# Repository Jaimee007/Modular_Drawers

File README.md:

# Modular_Drawers

Cajonera modular inteligente impresa en 3D. Cada unidad de retícula lleva su propio microcontrolador (CH32V003), un LED RGB y un final de carrera. Los módulos se unen con cola de milano y se conectan entre sí con latiguillos de cable plano IDC. Un ESP32-C3 en el módulo base **descubre automáticamente la posición de cada cajón** y lo integra con Home Assistant, para encender el cajón donde está lo que buscas.

## Documentación

La documentación está separada en cuatro niveles, del "qué" al "cómo". **Si solo vas a leer uno, lee el primero.**

| # | Archivo | Contenido | Cambia cuando… |
|---|---|---|---|
| 1 | [docs/01_especificacion_funcional.md](docs/01_especificacion_funcional.md) | **Qué hace el sistema**: requisitos, comportamiento, estados, criterios de aceptación. Sin un número de pin dentro | …cambia el comportamiento del producto |
| 2 | [docs/02_diseno_hardware.md](docs/02_diseno_hardware.md) | **Cómo está construido**: arquitectura, componentes, protocolo del bus, alimentación, mecánica | …se cambia un componente o una decisión técnica |
| 3 | [docs/03_diseno_pcb.md](docs/03_diseno_pcb.md) | **Las placas en KiCad**: esquemáticos, layout, reglas de diseño, pedido a JLCPCB | …se rediseña una placa |
| 4 | [docs/04_diseno_software.md](docs/04_diseno_software.md) | **El código**: firmware del módulo y del controlador, integración en HA, plan de pruebas por fases | …cambia el firmware |

Y aparte:

| Archivo | Contenido |
|---|---|
| [docs/bom_5_cajones.md](docs/bom_5_cajones.md) | Lista de materiales para un prototipo de 5 cajones, con referencias de LCSC y JLCPCB |

## Herramientas

- `tools/gen_esquematico.py`: genera un esquemático de referencia en HTML. Uso: `python tools/gen_esquematico.py` (solo librería estándar de Python).

## Resumen técnico

| | |
|---|---|
| **Retícula** | 50 mm. Profundidad 130 mm |
| **Un módulo = una unidad de retícula** | Un cajón 1×1 es un módulo; un 2×1 son dos módulos emparejados. **Una sola placa para todo** |
| **Micro por módulo** | CH32V003F4P6 (TSSOP-20), ~0,15 $ |
| **Dirección** | 1–31, por 5 puentes de soldadura |
| **Emparejamiento** | 2 puentes direccionales (pareja a la izquierda / abajo) |
| **Bus entre módulos** | Cable plano de 6 hilos: GND, 5V, DATA, SENSE, GND, 5V. **Box header 2×3 en las cuatro caras**; el cable nunca se suelda a la placa |
| **Posición automática** | Línea SENSE punto a punto entre vecinos. El usuario nunca configura posiciones |
| **Base** | ESP32-C3 SuperMini + una única entrada USB-C de 5 V para toda la cajonera |
| **Coste por módulo** | ~2,7 € |

## Estado del proyecto

| Fase | Estado |
|---|---|
| H0 · Compras | En curso |
| H1 · Protoboard | Pendiente |
| H2 · Placa perforada en armazones v1 | Pendiente |
| H3 · PCB en KiCad | **En curso** |
| H4 · Firmware e integración | Pendiente |

## Principios de diseño

Cuatro ideas que explican la mayoría de las decisiones:

1. **La posición se descubre, no se configura.** El usuario monta un cajón y el sistema averigua dónde está.
2. **Un cajón que se abre se ilumina aunque el controlador no responda.** La función más básica no depende de la red.
3. **En la PCB solo se suelda el conector; el cable nunca toca la placa.** Los cables son consumibles reemplazables.
4. **Las placas son pequeñas y flotantes.** No cumplen funciones mecánicas: para llegar a los sitios están los cables. Esto desacopla el diseño electrónico del diseño 3D.

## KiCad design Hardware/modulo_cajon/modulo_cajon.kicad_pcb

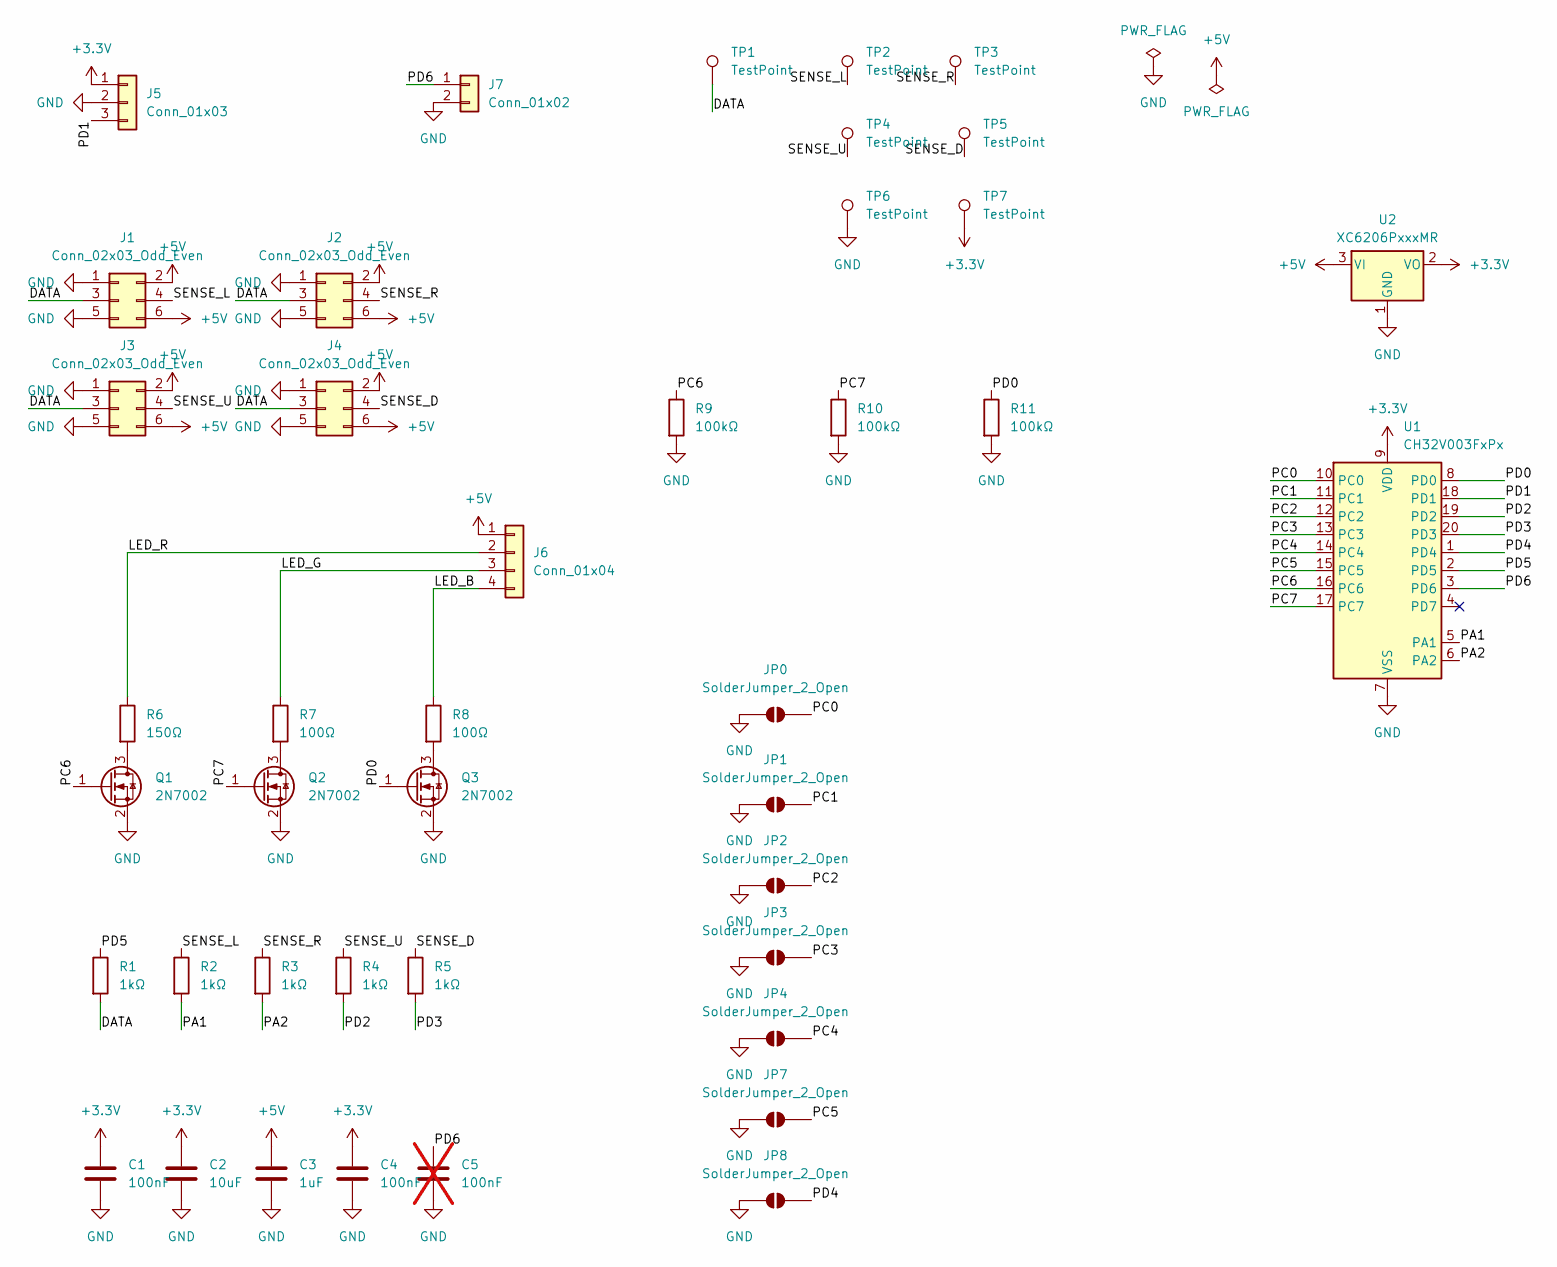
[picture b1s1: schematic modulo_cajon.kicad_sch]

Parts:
C1, C4: 100nF; C_0603_1608Metric
C2: 10uF; C_0805_2012Metric
C3: 1uF; C_0603_1608Metric
C5: 100nF; C_0603_1608Metric; not fitted
J1, J2, J3, J4: Conn_02x03_Odd_Even; IDC-Header_2x03_P2.54mm_Vertical
J5: Conn_01x03; PinHeader_1x03_P2.54mm_Vertical
J6: Conn_01x04; PinHeader_1x04_P2.54mm_Vertical
J7: Conn_01x02; PinHeader_1x02_P2.54mm_Vertical
JP0, JP1, JP2, JP3, JP4, JP7, JP8: SolderJumper_2_Open; SolderJumper-2_P1.3mm_Open_Pad1.0x1.5mm
Q1, Q2, Q3: 2N7002; SOT-23
R1, R2, R3, R4, R5: 1kΩ; R_0603_1608Metric
R6: 150Ω; R_0603_1608Metric
R7, R8: 100Ω; R_0603_1608Metric
R9, R10, R11: 100kΩ; R_0603_1608Metric
TP1, TP2, TP3, TP4, TP5, TP6, TP7: TestPoint; TestPoint_Pad_D1.5mm
U1: CH32V003FxPx; TSSOP-20_4.4x6.5mm_P0.65mm
U2: XC6206PxxxMR; SOT-23-3

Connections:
+3.3V: C1.1, C2.1, C4.1, J5.1, TP7.1 (1_1), U1.9 (VDD), U2.2 (VO)
+5V: C3.1, J1.2, J1.6, J2.2, J2.6, J3.2, J3.6, J4.2, J4.6, J6.1, U2.3 (VI)
/DATA: J1.3, J2.3, J3.3, J4.3, R1.2, TP1.1 (1_1)
/LED_B: J6.4, R8.1
/LED_G: J6.3, R7.1
/LED_R: J6.2, R6.1
/PA1: R2.2, U1.5 (PA1)
/PA2: R3.2, U1.6 (PA2)
/PC0: JP0.2 (B), U1.10 (PC0)
/PC1: JP1.2 (B), U1.11 (PC1)
/PC2: JP2.2 (B), U1.12 (PC2)
/PC3: JP3.2 (B), U1.13 (PC3)
/PC4: JP4.2 (B), U1.14 (PC4)
/PC5: JP7.2 (B), U1.15 (PC5)
/PC6: Q1.1 (G), R9.1, U1.16 (PC6)
/PC7: Q2.1 (G), R10.1, U1.17 (PC7)
/PD0: Q3.1 (G), R11.1, U1.8 (PD0)
/PD1: J5.3, U1.18 (PD1)
/PD2: R4.2, U1.19 (PD2)
/PD3: R5.2, U1.20 (PD3)
/PD4: JP8.2 (B), U1.1 (PD4)
/PD5: R1.1, U1.2 (PD5)
/PD6: C5.1, J7.1, U1.3 (PD6)
/SENSE_D: J4.4, R5.1, TP5.1 (1_1)
/SENSE_L: J1.4, R2.1, TP2.1 (1_1)
/SENSE_R: J2.4, R3.1, TP3.1 (1_1)
/SENSE_U: J3.4, R4.1, TP4.1 (1_1)
GND: C1.2, C2.2, C3.2, C4.2, C5.2, J1.1, J1.5, J2.1, J2.5, J3.1, J3.5, J4.1, J4.5, J5.2, J7.2, JP0.1 (A), JP1.1 (A), JP2.1 (A), JP3.1 (A), JP4.1 (A), JP7.1 (A), JP8.1 (A), Q1.2 (S), Q2.2 (S), Q3.2 (S), R9.2, R10.2, R11.2, TP6.1 (1_1), U1.7 (VSS), U2.1 (GND)
unnamed: Q1.3 (D), R6.2
unnamed: Q2.3 (D), R7.2
unnamed: Q3.3 (D), R8.2

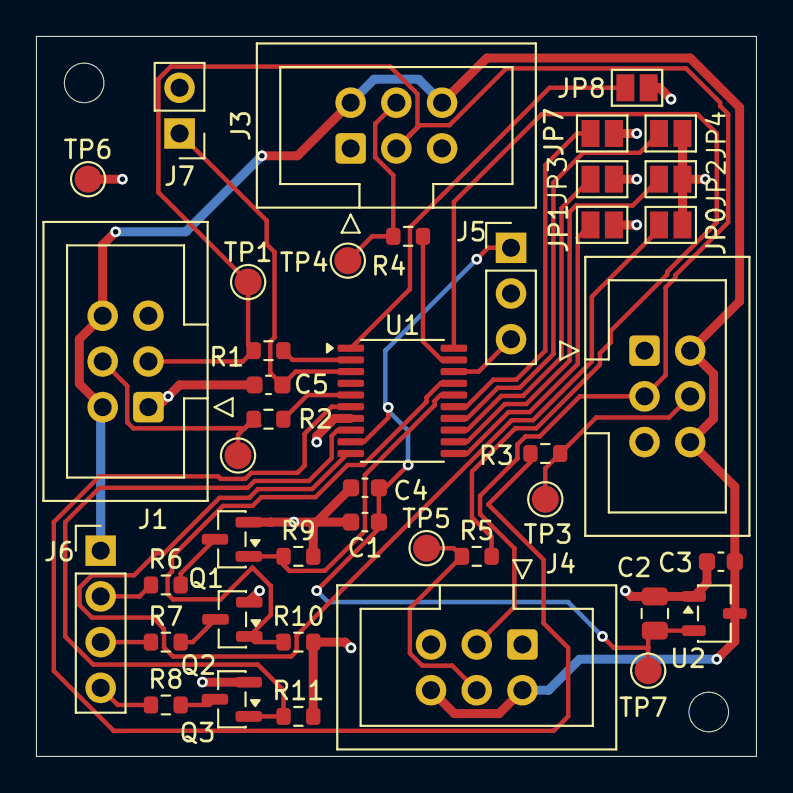
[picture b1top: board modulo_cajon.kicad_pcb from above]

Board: 2 copper layers, 40.0 x 40.0 mm, 42 parts (0 on the bottom side), 31 nets.

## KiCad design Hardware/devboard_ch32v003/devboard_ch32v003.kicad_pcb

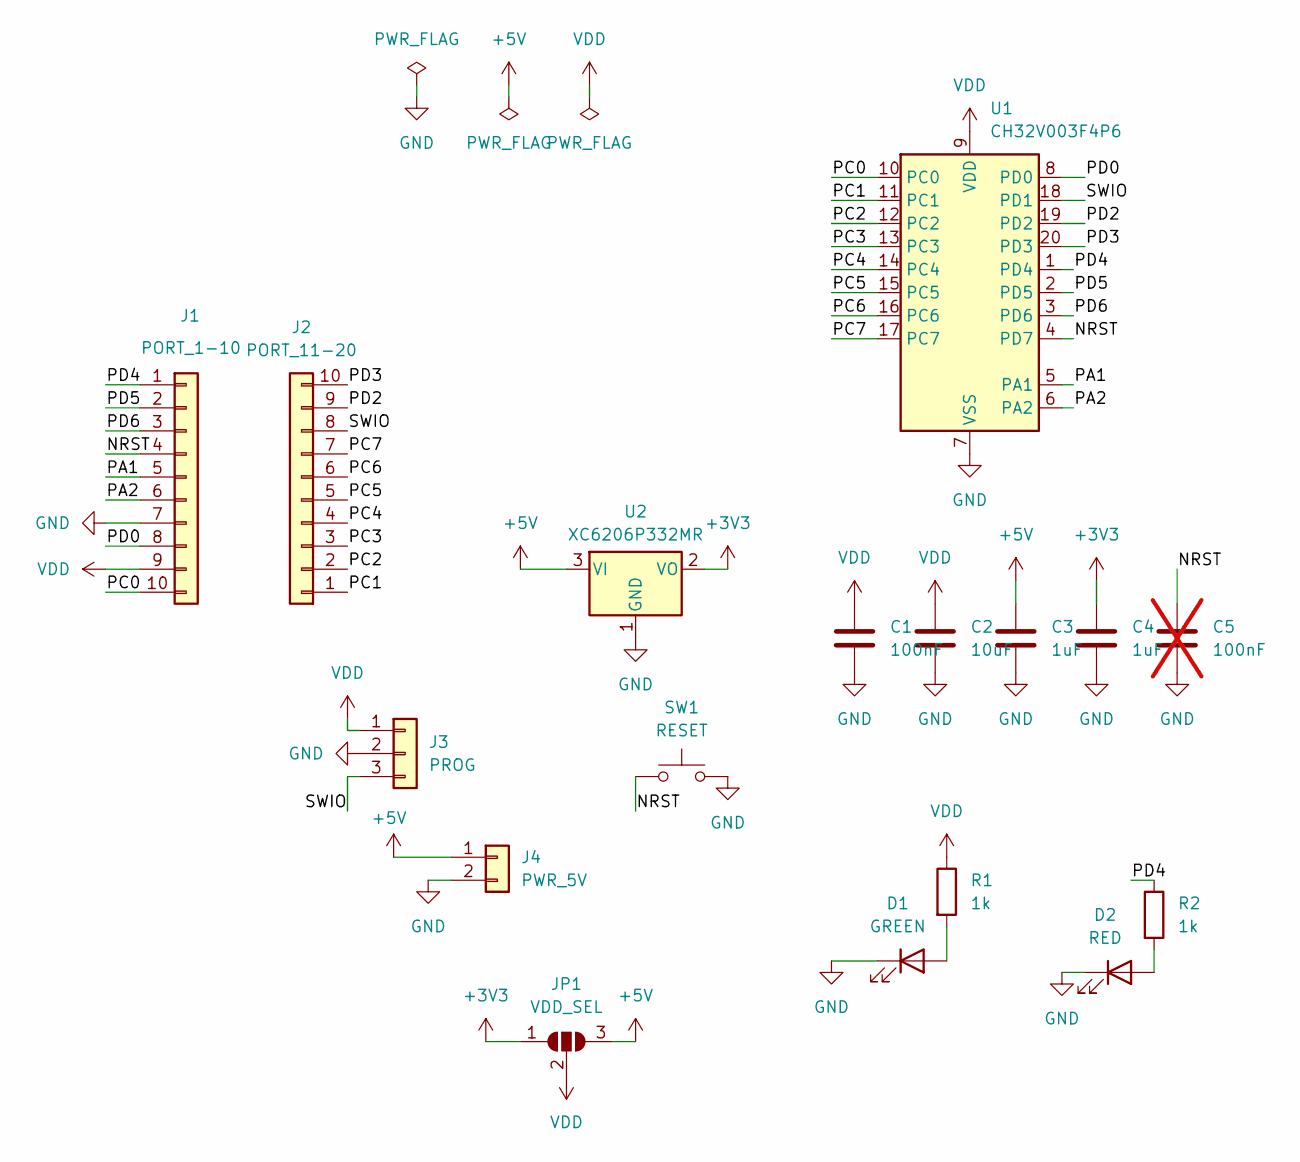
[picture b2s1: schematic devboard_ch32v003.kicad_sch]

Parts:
C1: 100nF; C_0603_1608Metric
C2: 10uF; C_0805_2012Metric
C3, C4: 1uF; C_0603_1608Metric
C5: 100nF; C_0603_1608Metric; not fitted
D1: GREEN; LED_0603_1608Metric
D2: RED; LED_0603_1608Metric
J1: PORT_1-10; PinHeader_1x10_P2.54mm_Vertical
J2: PORT_11-20; PinHeader_1x10_P2.54mm_Vertical
J3: PROG; PinHeader_1x03_P2.54mm_Vertical
J4: PWR_5V; PinHeader_1x02_P2.54mm_Vertical
JP1: VDD_SEL; SolderJumper-3_P1.3mm_Open_Pad1.0x1.5mm
R1, R2: 1k; R_0603_1608Metric
SW1: RESET; SW_PUSH_6mm
U1: CH32V003F4P6; TSSOP-20_4.4x6.5mm_P0.65mm
U2: XC6206P332MR; SOT-23-3

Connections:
+3V3: C4.1, JP1.1 (A), U2.2 (VO)
+5V: C3.1, J4.1, JP1.3 (B), U2.3 (VI)
/NRST: C5.1, J1.4, SW1.1, U1.4 (PD7)
/PA1: J1.5, U1.5 (PA1)
/PA2: J1.6, U1.6 (PA2)
/PC0: J1.10, U1.10 (PC0)
/PC1: J2.1, U1.11 (PC1)
/PC2: J2.2, U1.12 (PC2)
/PC3: J2.3, U1.13 (PC3)
/PC4: J2.4, U1.14 (PC4)
/PC5: J2.5, U1.15 (PC5)
/PC6: J2.6, U1.16 (PC6)
/PC7: J2.7, U1.17 (PC7)
/PD0: J1.8, U1.8 (PD0)
/PD2: J2.9, U1.19 (PD2)
/PD3: J2.10, U1.20 (PD3)
/PD4: J1.1, R2.1, U1.1 (PD4)
/PD5: J1.2, U1.2 (PD5)
/PD6: J1.3, U1.3 (PD6)
/SWIO: J2.8, J3.3, U1.18 (PD1)
GND: C1.2, C2.2, C3.2, C4.2, C5.2, D1.1 (K), D2.1 (K), J1.7, J3.2, J4.2, SW1.2, U1.7 (VSS), U2.1 (GND)
unnamed: D1.2 (A), R1.2
unnamed: D2.2 (A), R2.2
VDD: C1.1, C2.1, J1.9, J3.1, JP1.2 (C), R1.1, U1.9 (VDD)

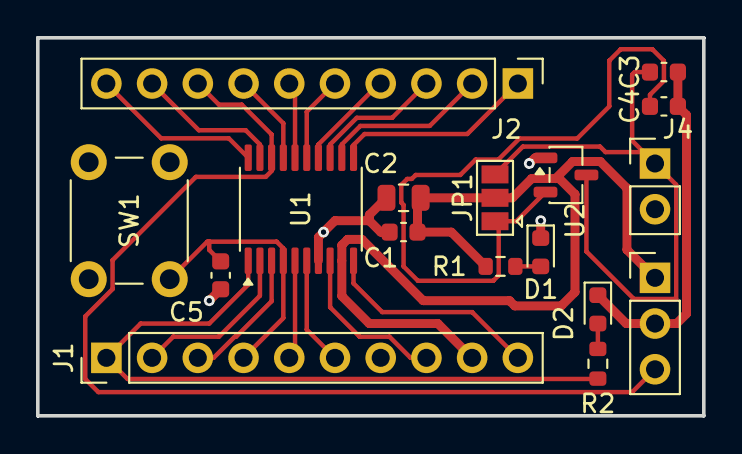
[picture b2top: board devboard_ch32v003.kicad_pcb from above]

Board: 2 copper layers, 37.0 x 21.0 mm, 17 parts (0 on the bottom side), 24 nets.

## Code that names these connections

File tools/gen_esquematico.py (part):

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    s.t(40,980,'Solo en el 2×1: J5 (SUPERIOR u1, coleta) → SENSE_T2 y',10,'start','#888',it=True)
    s.t(40,996,'J6 (INFERIOR u1, conector macho) → SENSE_B2, mismo pinout.',10,'start','#888',it=True)
    # MCU
    left=[(9,'VDD'),(7,'VSS'),(2,'PD5'),(5,'PA1'),(6,'PA2'),(19,'PD2'),(20,'PD3'),(1,'PD4'),(17,'PC7')]
    right=[(16,'PC6'),(3,'PD6'),(10,'PC0'),(11,'PC1'),(12,'PC2'),(13,'PC3'),(14,'PC4'),(8,'PD0'),(15,'PC5'),(18,'PD1/SWIO'),(4,'PD7/NRST')]
    pl=s.ic(640,230,190,470,'U1  CH32V003F4P6','TSSOP-20 · JLCPCB C5187096',left,right)
    x,y=pl['VDD']; s.wire([(x,y),(x-40,y)]); s.net(x-40,y,'3V3','left')
    x,y=pl['VSS']; s.wire([(x,y),(x-40,y)]); s.net(x-40,y,'GND','left')
    rows=[('PD5','R1','DATA','bus DATA (UART half-duplex)'),('PA1','R2','SENSE_L',''),('PA2','R3','SENSE_R',''),
          ('PD2','R4','SENSE_T',''),('PD3','R5','SENSE_B',''),('PD4','R6','SENSE_T2','solo 2×1'),('PC7','R7','SENSE_B2','solo 2×1')]
    for pin,r,n,note in rows:
        x,y=pl[pin]; s.wire([(x,y),(x-10,y)]); s.res_h(x-50,y,r,'1k'); s.wire([(x-50,y),(x-70,y)]); s.net(x-70,y,n,'left')
        if note: s.t(x-74-8-7.2*len(n)-12,y+4,note,9,'end','#888',it=True)
    # LED
    x,y=pl['PC6']  # 870,270
    s.wire([(x,y),(x+20,y)]); s.res_h(x+20,y,'R8','330Ω'); s.wire([(x+60,y),(1010,y)])
    s.rect(1010,240,120,80,fill='#fffbe8',sw=2)
    s.t(1070,236-0,'',1)
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    s.t(1230,140,'la señal de 3,3 V del micro.',10,'start','#666')
    s.wire([(1130,280),(1220,280)]); s.t(1226,284,'→ LED2 DIN (solo 2×1)',10,'start','#888',it=True)
    # switch
    x,y=pl['PD6']; s.wire([(x,y),(x+30,y)]); s.net(x+30,y,'SW_CAJON','right')
    s.t(1180,375,'Final de carrera',12,'start','#444','bold')
    s.net(1210,410,'SW_CAJON','left'); s.wire([(1210,410),(1240,410)]); s.switch(1240,410,'SW1','DM1-12UP-1 · C405949'); s.wire([(1300,410),(1360,410)]); s.gnd(1360,410)
    s.t(1180,450,'COM → GND · NO → PD6 (pull-up interna)',10,'start','#666')
    s.t(1180,465,'Pulsado = cajón cerrado = 0 · Abierto = 1',10,'start','#666')
    # jumpers
    names=[('PC0','JP0','×1'),('PC1','JP1','×2'),('PC2','JP2','×4'),('PC3','JP3','×8'),('PC4','JP4','×16'),('PD0','JP5','×32'),('PC5','JP6','tamaño')]
    for pin,j,nt in names:
        x,y=pl[pin]; s.wire([(x,y),(x+10,y)]); s.jumper(x+10,y,j); s.wire([(x+50,y),(x+60,y)])
        s.t(x+64,y+4,'GND',10,'start',COL['GND'],'bold'); s.t(x+96,y+4,nt,10,'start','#888')
    x,y=pl['PD1/SWIO']; s.wire([(x,y),(x+30,y)]); s.tp(x+36,y,'TP1 SWIO (programación)')
    x,y=pl['PD7/NRST']; s.wire([(x,y),(x+30,y)]); s.tp(x+36,y,'TP2 NRST (opcional)')
    s.tp(906,720,'TP3 → 3V3'); s.tp(1036,720,'TP4 → GND')
    s.t(870,745,'TP1+TP3+TP4 = pads para la punta del WCH-LinkE',10,'start','#666')
    # notes box
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         '• JP6 abierto = 1×1 · cerrado = 2×1.',
         '• SENSE: entrada con pull-up interna;',
         '   para avisar, el micro solo lo tira a 0.',
         '• PD5: USART half-duplex en open-drain',
         '   (el pull-up del bus está en la base).',
         '• 5V, GND y DATA de J1–J4, en paralelo.',
         '• Sin condensadores grandes en 5V',
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    for i,(n,c) in enumerate(lg):
        s.rect(40+i*150,1032,14,14,fill=c,stroke=c); s.t(60+i*150,1044,n,11)
    s.t(40,1070,'▮ = pin del conector macho 2×3 (la pestaña blanca marca la muesca)   ○ = pad donde se suelda un hilo de la coleta (hilo rojo = pin 1 = GND)   1k = 1 kΩ',11,'start','#666')
    s.t(40,1094,'Pinout CH32V003F4P6 (TSSOP-20): 1 PD4 · 2 PD5 · 3 PD6 · 4 PD7 · 5 PA1 · 6 PA2 · 7 VSS · 8 PD0 · 9 VDD · 10 PC0 · 11 PC1 · 12 PC2 · 13 PC3 · 14 PC4 · 15 PC5 · 16 PC6 · 17 PC7 · 18 PD1 · 19 PD2 · 20 PD3',10,'start','#888')
    return s.svg()

# ================= HOJA 3: BASE =================
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    s.wire([(x+130,y),(x+130,y-60)]); s.res_v(x+130,y-100,'R10','4,7k'); s.wire([(x+130,y-100),(x+130,y-110)]); s.net(x+130,y-110,'3V3','right')
    s.t(x+170,y-30,'TX solo puede tirar DATA a 0 (cátodo hacia TX).',10,'start','#666',it=True)
    s.t(x+170,y-16,'R10 es el único pull-up de todo el bus.',10,'start','#666',it=True)
    for pin,r,n in [('GPIO0','R11','SENSE_L'),('GPIO1','R12','SENSE_R'),('GPIO3','R13','SENSE_T'),('GPIO4','R14','SENSE_B')]:
        x,y=pl[pin]; s.wire([(x,y),(x+10,y)]); s.res_h(x+10,y,r,'1k'); s.wire([(x+50,y),(x+70,y)]); s.net(x+70,y,n,'right')
    x,y=pl['GPIO7']; s.wire([(x,y),(x+20,y)]); s.switch(x+20,y,'','SW10 · final de carrera'); s.wire([(x+80,y),(x+140,y)]); s.gnd(x+140,y)
    x,y=pl['GPIO10']; s.wire([(x,y),(x+10,y)]); s.res_h(x+10,y,'R15','330Ω'); s.wire([(x+50,y),(x+70,y)]); s.t(x+76,y+4,'→ DIN LED10 (SK6812RGBW, mismo circuito que el cajón: D1 + C4)',10,'start','#666')
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        for yy,n,c in lines: s.wire([(bx+40,yy),(bx+340,yy)],c=c,w=2.4)
        s.rect(bx+120,380,140,80,fill='#fffbe8',sw=2,rx=2)
        s.t(bx+190,404,'CH32V003',12,'middle','#222','bold'); s.t(bx+190,420,f'JP → dir {addr}',10,'middle','#666')
        s.t(bx+126,446,'PA1',10); s.t(bx+254,446,'PA2',10,'end'); s.t(bx+190,392+0,'',1)
        # DATA tap
        s.dot(bx+190,yD,COL['DATA']); s.wire([(bx+190,yD),(bx+190,380)],c=COL['DATA'],w=2.4); s.t(bx+186,yD+40,'R1 → PD5',9,'end',COL['DATA'])
        # 5V tap to LDO
        s.dot(bx+132,y5,COL['5V']); s.wire([(bx+132,y5),(bx+132,380)],c=COL['5V'],w=1.6,dash='4 3'); s.t(bx+126,y5+60,'5V → U2',9,'end',COL['5V'])
        s.dot(bx+230,yG,COL['GND']); s.wire([(bx+230,yG),(bx+230,380)],c=COL['GND'],w=1.6,dash='4 3')
        # sense
        s.wire([(bx+40,yS),(bx+80,yS),(bx+80,442),(bx+120,442)],c='#1e9e57',w=2.4); s.t(bx+86,yS+18,'R2 1k',9,'start','#1e9e57')
        s.wire([(bx+340,yS),(bx+300,yS),(bx+300,442),(bx+260,442)],c='#1e9e57',w=2.4); s.t(bx+294,yS+18,'R3 1k',9,'end','#1e9e57')
        s.t(bx+190,478,'J3 (arriba) y J4 (abajo): igual, SENSE_T → PD2, SENSE_B → PD3',9,'middle','#888',it=True)
    drawer(560,1); drawer(1080,2)
    # mating links
    for xa,xb in [(420,560),(940,1080)]:
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            s.t((xa+xb)/2,yy-5,n,10,'middle',c,'bold')
    # descriptive text
    s.t(40,525,'• GND, 5V y DATA son el mismo cable en los tres módulos (bus en paralelo): la base alimenta y habla con todos.',12,'start','#333')
    s.t(40,546,'• SENSE va de punto a punto: el GPIO1 de la base solo llega al PA1 del cajón #1, y el PA2 del cajón #1 solo llega al PA1 del cajón #2.',12,'start','#333')
    s.t(40,567,'• Descubrimiento: la base tira a 0 GPIO1 → el cajón 1 lo ve en PA1 (izquierda) → está en (1,0). El cajón 1 tira a 0 PA2 → el cajón 2 lo ve en PA1 → está en (2,0).',12,'start','#333')
    return s.svg()

page=f'''<!doctype html><html lang="es"><head><meta charset="utf-8"><title>Esquemático · cajonera modular · base + 2 cajones</title>
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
